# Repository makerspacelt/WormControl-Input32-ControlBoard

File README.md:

---

WormControl Inputs Control board

NOTE: This is only a prototype now, so things might not work and everything might change 

Basic target features:

* Compatibility with esphome and Home Assistant

Dev NOTE: before commit, run `./kibot.sh` to regenerate documentation, bom, gerbers and other assets.

* [schematics.pdf](gen/schematics.pdf)
* [pcb.pdf with dimensions](gen/pcb.pdf)
* [ibom.html](gen/single/ibom.html)

---

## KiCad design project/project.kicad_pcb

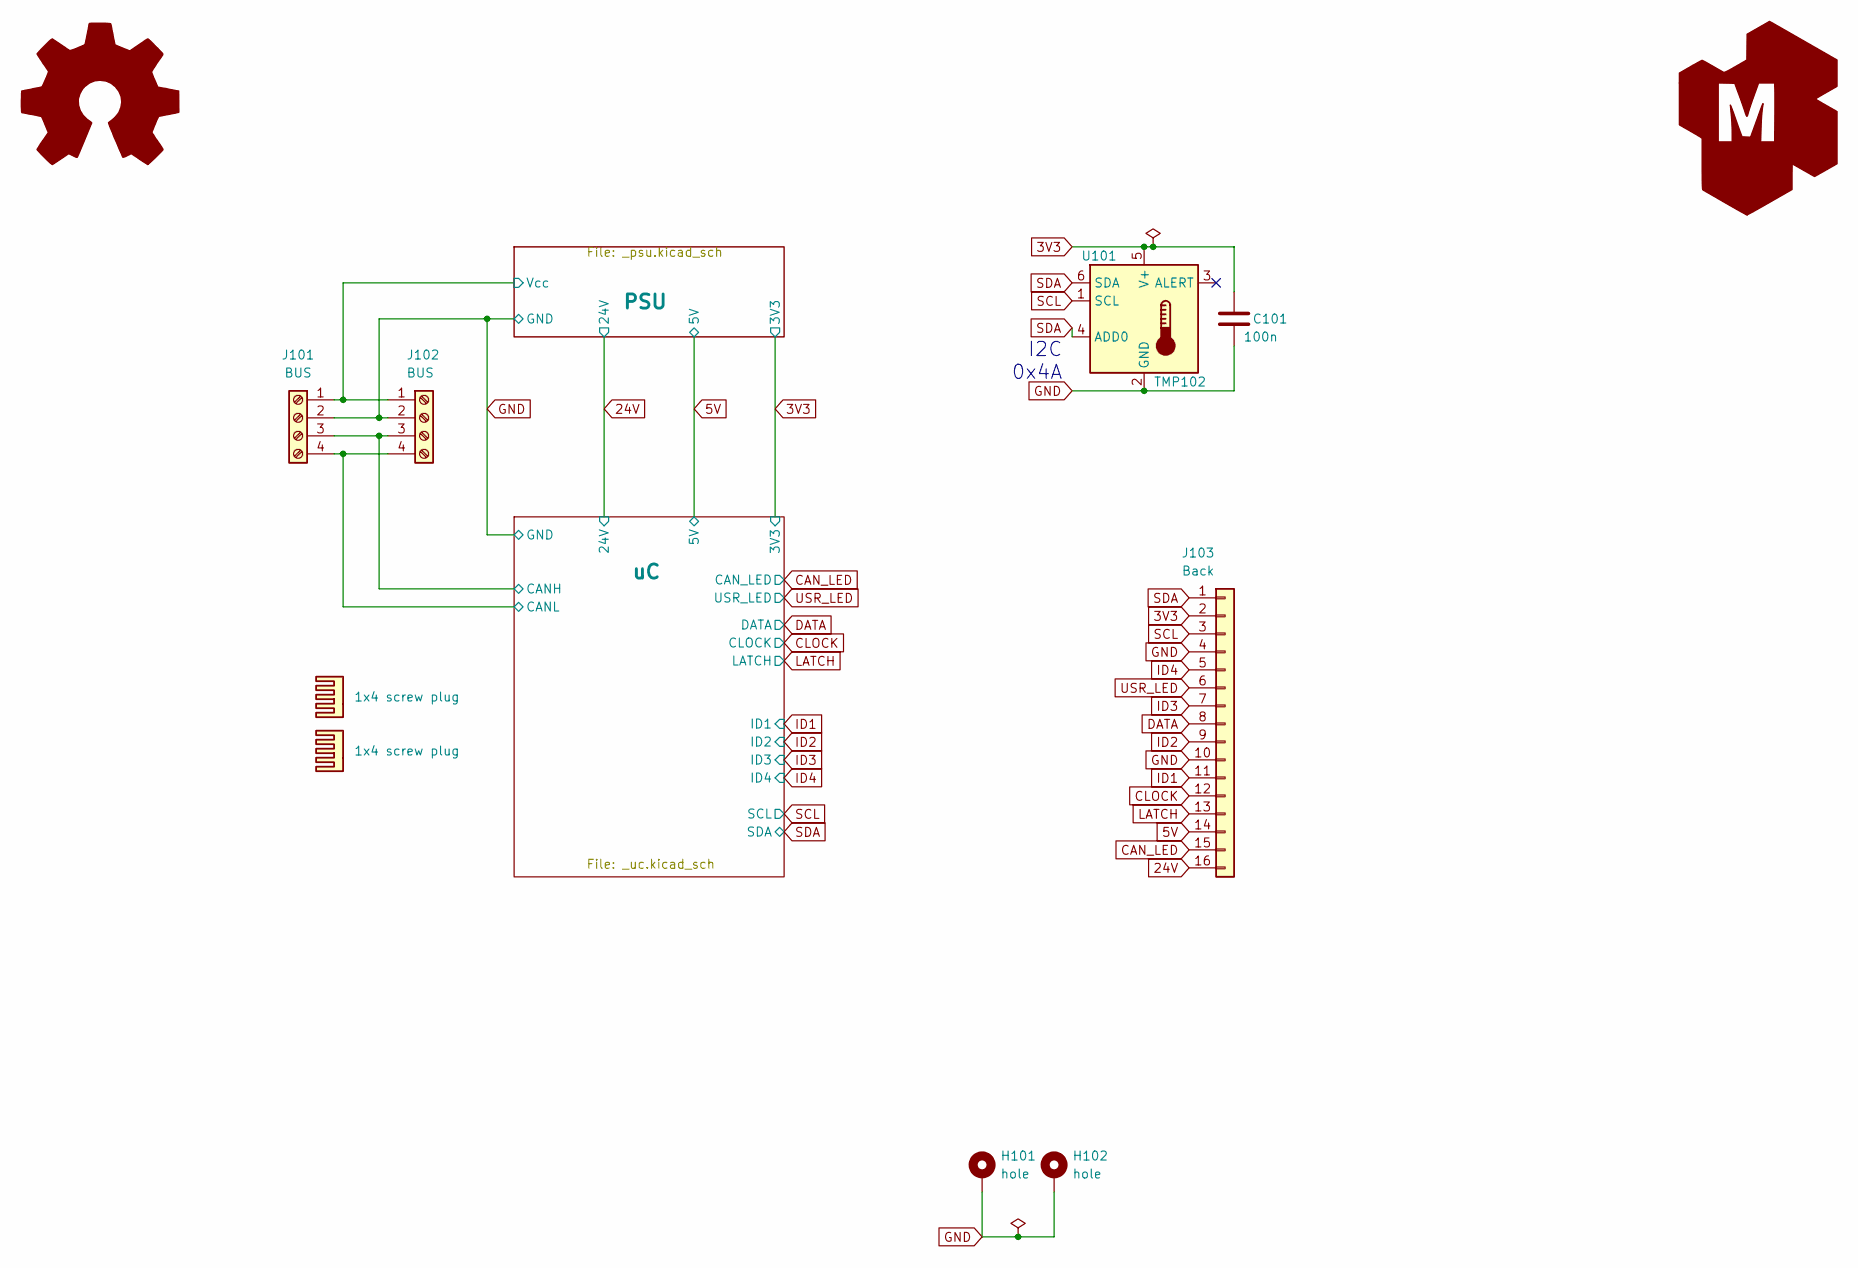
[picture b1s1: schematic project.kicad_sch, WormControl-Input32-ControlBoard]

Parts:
BOM101, BOM102: 1x4 screw plug; jlc-part-type E
C101: 100n; C_0805_2012Metric_Pad1.18x1.45mm_HandSolder; jlc-part-type B
G101: Logo_Open_Hardware_Large; OSHW-Symbol_6.7x6mm_SilkScreen
G102: LOGO_KMS; logo_kms_small_silkscreen
H101, H102: hole; MountingHole_3.2mm_M3_Pad_Via
J101, J102: BUS; PhoenixContact_MCV_1,5_4-G-3.5_1x04_P3.50mm_Vertical; jlc-part-type E
J103: Back; PinSocket_2x08_P2.54mm_Vertical_SMD; lcsc# C3975153
U101: TMP102; SOT-563; jlc-part-type E

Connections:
3V3: C101.1, J103.2, U101.5 (V+); also elsewhere on the board
5V: J103.14; also elsewhere on the board
24V: J103.16; also elsewhere on the board
/PSU/Vcc: J101.1, J102.1; also elsewhere on the board
/uC/CANH: J101.3, J102.3; also elsewhere on the board
/uC/CANL: J101.4, J102.4; also elsewhere on the board
CAN_LED: J103.15; also elsewhere on the board
CLOCK: J103.12; also elsewhere on the board
DATA: J103.8; also elsewhere on the board
GND: C101.2, H101.1, H102.1, J101.2, J102.2, J103.4, J103.10, U101.2 (GND); also elsewhere on the board
ID1: J103.11; also elsewhere on the board
ID2: J103.9; also elsewhere on the board
ID3: J103.7; also elsewhere on the board
ID4: J103.5; also elsewhere on the board
LATCH: J103.13; also elsewhere on the board
SCL: J103.3, U101.1 (SCL); also elsewhere on the board
SDA: J103.1, U101.4 (ADD0), U101.6 (SDA); also elsewhere on the board
USR_LED: J103.6; also elsewhere on the board

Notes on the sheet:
I2C 0x4A

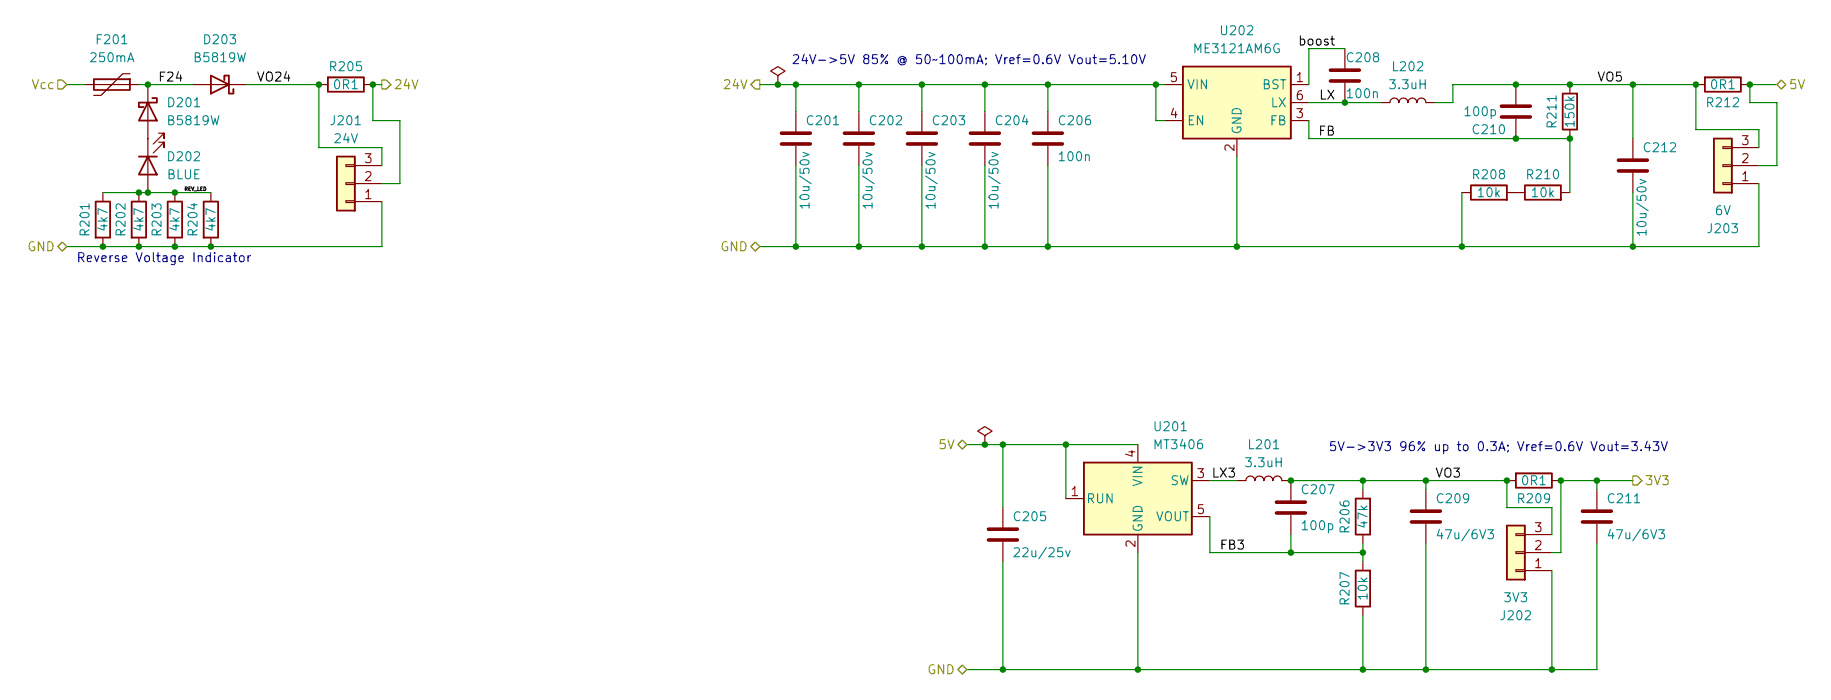
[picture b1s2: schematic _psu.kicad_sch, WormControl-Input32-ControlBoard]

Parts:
C201, C202, C203, C204, C212: 10u/50v; C_0805_2012Metric_Pad1.18x1.45mm_HandSolder; jlc-part-type B
C205: 22u/25v; C_0805_2012Metric_Pad1.18x1.45mm_HandSolder; jlc-part-type B
C206, C208: 100n; C_0805_2012Metric_Pad1.18x1.45mm_HandSolder; jlc-part-type B
C207, C210: 100p; C_0805_2012Metric_Pad1.18x1.45mm_HandSolder; jlc-part-type B
C209, C211: 47u/6V3; C_0805_2012Metric_Pad1.18x1.45mm_HandSolder; jlc-part-type B
D201, D203: B5819W; D_SOD-123; jlc-part-type B
D202: BLUE; LED_0805_2012Metric_Pad1.15x1.40mm_HandSolder; jlc-part-type B
F201: 250mA; Fuse_0805_2012Metric_Pad1.15x1.40mm_HandSolder; lcsc# C22378353
J201: 24V; PinHeader_1x03_P2.54mm_Vertical
J202: 3V3; PinHeader_1x03_P2.54mm_Vertical
J203: 6V; PinHeader_1x03_P2.54mm_Vertical
L201, L202: 3.3uH; L_1008_2520Metric_Pad1.43x2.20mm_HandSolder; jlc-part-type E
R201, R202, R203, R204: 4k7; R_0805_2012Metric_Pad1.20x1.40mm_HandSolder; jlc-part-type B
R205, R209, R212: 0R1; R_0805_2012Metric_Pad1.20x1.40mm_HandSolder; jlc-part-type E
R206: 47k; R_0805_2012Metric_Pad1.20x1.40mm_HandSolder; jlc-part-type B
R207, R208, R210: 10k; R_0805_2012Metric_Pad1.20x1.40mm_HandSolder; jlc-part-type B
R211: 150k; R_0805_2012Metric_Pad1.20x1.40mm_HandSolder; jlc-part-type B
U201: MT3406; TSOT-23-5; jlc-part-type E
U202: ME3121AM6G; SOT-23-6; jlc-part-type E

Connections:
3V3: C211.1, J202.2, R209.1; also elsewhere on the board
5V: C205.1, J203.2, R212.1, U201.1 (RUN), U201.4 (VIN); also elsewhere on the board
24V: C201.1, C202.1, C203.1, C204.1, C206.1, J201.2, R205.1, U202.4 (EN), U202.5 (VIN); also elsewhere on the board
/PSU/F24: D201.1 (K), D203.2 (A), F201.1
/PSU/FB: C210.1, R210.2, R211.1, U202.3 (FB)
/PSU/FB3: C207.2, R206.1, R207.2, U201.5 (VOUT)
/PSU/LX: C208.2, L202.1, U202.6 (LX)
/PSU/LX3: L201.1, U201.3 (SW)
/PSU/REV_LED: D202.2 (A), R201.1, R202.1, R203.1, R204.1
/PSU/VO3: C207.1, C209.1, J202.3, L201.2, R206.2, R209.2
/PSU/VO5: C210.2, C212.1, J203.3, L202.2, R211.2, R212.2
/PSU/VO24: D203.1 (K), J201.3, R205.2
/PSU/Vcc: F201.2; also elsewhere on the board
/PSU/boost: C208.1, U202.1 (BST)
GND: C201.2, C202.2, C203.2, C204.2, C205.2, C206.2, C209.2, C211.2, C212.2, J201.1, J202.1, J203.1, R201.2, R202.2, R203.2, R204.2, R207.1, R208.1, U201.2 (GND), U202.2 (GND); also elsewhere on the board
unnamed: D201.2 (A), D202.1 (K)
unnamed: R208.2, R210.1

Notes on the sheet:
24V->5V 85% @ 50~100mA; Vref=0.6V Vout=5.10V
5V->3V3 96% up to 0.3A; Vref=0.6V Vout=3.43V
Reverse Voltage Indicator

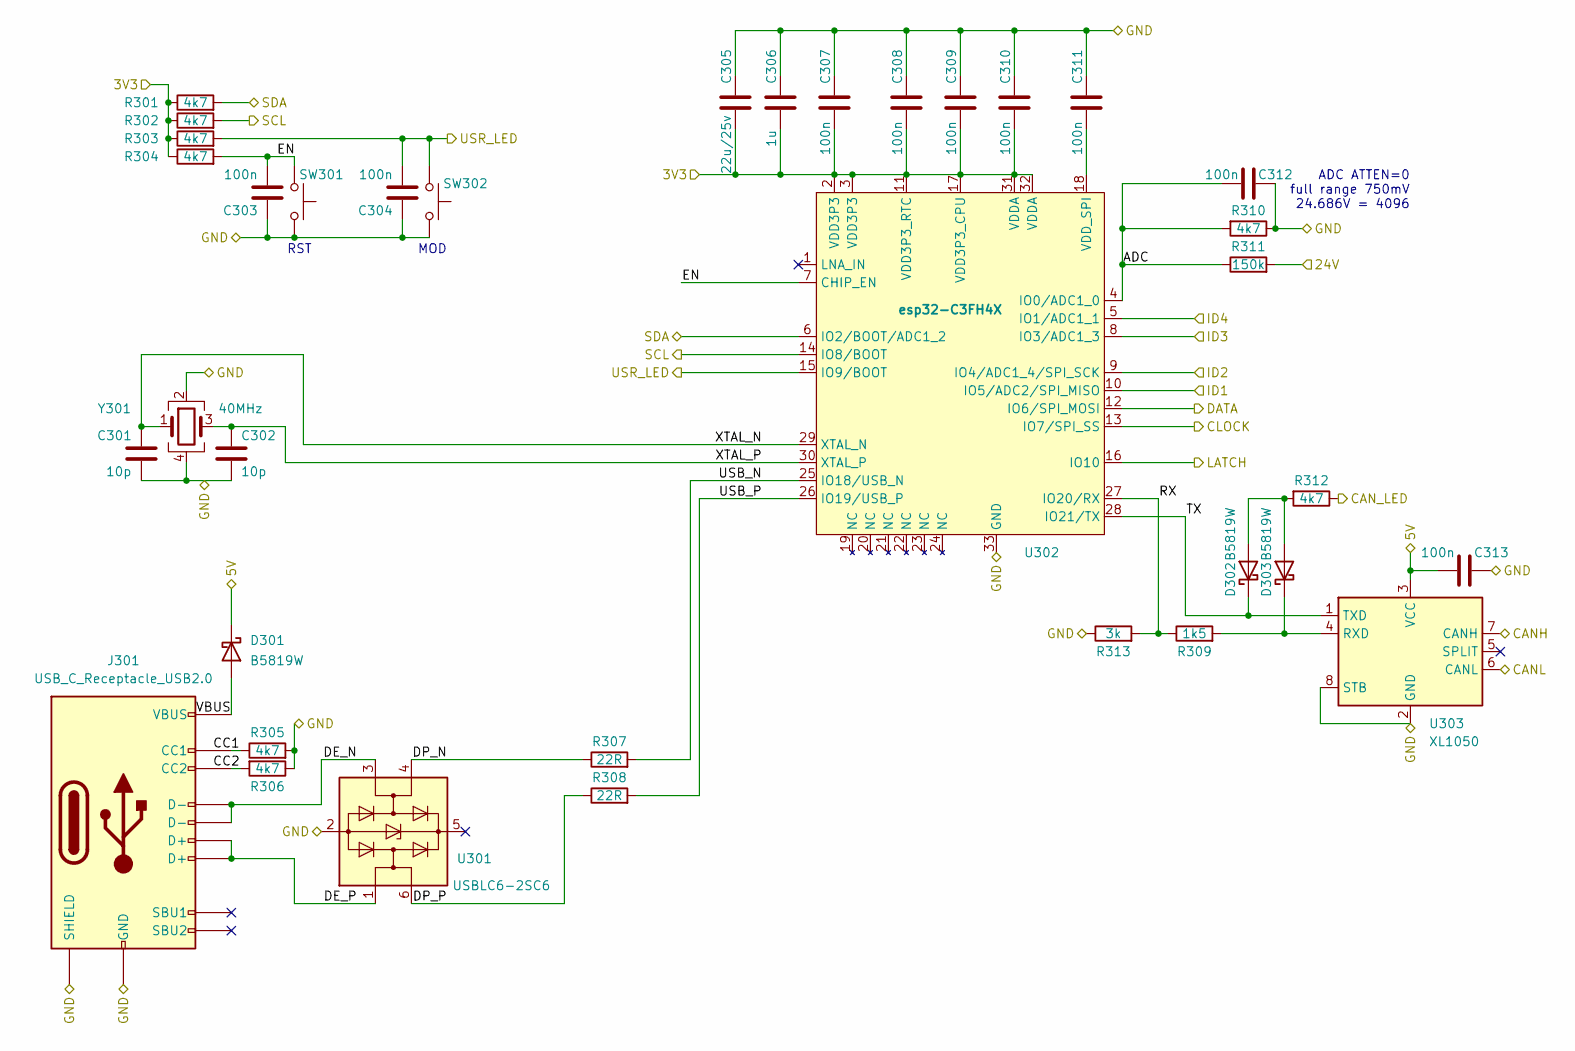
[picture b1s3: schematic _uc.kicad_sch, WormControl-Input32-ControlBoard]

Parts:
C301, C302: 10p; C_0402_1005Metric_Pad0.74x0.62mm_HandSolder; jlc-part-type B
C303, C304, C307, C308, C309, C310, C311, C312, C313: 100n; C_0805_2012Metric_Pad1.18x1.45mm_HandSolder; jlc-part-type B
C305: 22u/25v; C_0805_2012Metric_Pad1.18x1.45mm_HandSolder; jlc-part-type B
C306: 1u; C_0805_2012Metric_Pad1.18x1.45mm_HandSolder; jlc-part-type B
D301, D302, D303: B5819W; D_SOD-123; jlc-part-type B
J301: USB_C_Receptacle_USB2.0; USB_C_Receptacle_G-Switch_GT-USB-7082G; jlc-part-type E
R301, R302, R303, R304, R305, R306, R310, R312: 4k7; R_0805_2012Metric_Pad1.20x1.40mm_HandSolder; jlc-part-type B
R307, R308: 22R; R_0805_2012Metric_Pad1.20x1.40mm_HandSolder; jlc-part-type B
R309: 1k5; R_0805_2012Metric_Pad1.20x1.40mm_HandSolder; jlc-part-type B
R311: 150k; R_0805_2012Metric_Pad1.20x1.40mm_HandSolder; jlc-part-type B
R313: 3k; R_0805_2012Metric_Pad1.20x1.40mm_HandSolder; jlc-part-type B
SW301, SW302: 15mm; SW_SPST_15; jlc-part-type E
U301: USBLC6-2SC6; SOT-23-6; jlc-part-type E
U302: esp32-C3FH4X; QFN-32-1EP_5x5mm_P0.5mm_EP3.65x3.65mm; jlc-part-type E
U303: XL1050; SOIC-8_3.9x4.9mm_P1.27mm; jlc-part-type E
Y301: 40MHz; Crystal_SMD_2016-4Pin_2.0x1.6mm; jlc-part-type E

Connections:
3V3: C305.2, C306.2, C307.1, C308.1, C309.1, C310.1, R301.1, R302.1, R303.1, R304.1, U302.2 (VDD3P3), U302.3 (VDD3P3), U302.11 (VDD3P3_RTC), U302.17 (VDD3P3_CPU), U302.31 (VDDA), U302.32 (VDDA); also elsewhere on the board
5V: C313.1, D301.1 (K), U303.3 (VCC); also elsewhere on the board
24V: R311.2; also elsewhere on the board
/uC/ADC: C312.1, R310.2, R311.1, U302.4 (IO0/ADC1_0)
/uC/CANH: U303.7 (CANH); also elsewhere on the board
/uC/CANL: U303.6 (CANL); also elsewhere on the board
/uC/CC1: J301.A5 (CC1), R305.1
/uC/CC2: J301.B5 (CC2), R306.2
/uC/DE_N: J301.A7 (D-), J301.B7 (D-), U301.3 (I/O2)
/uC/DE_P: J301.A6 (D+), J301.B6 (D+), U301.1 (I/O1)
/uC/DP_N: R307.1, U301.4 (I/O2)
/uC/DP_P: R308.1, U301.6 (I/O1)
/uC/EN: C303.2, R304.2, SW301.1, U302.7 (CHIP_EN)
/uC/RX: R309.1, R313.2, U302.27 (IO20/RX)
/uC/TX: D302.1 (K), U302.28 (IO21/TX), U303.1 (TXD)
/uC/USB_N: R307.2, U302.25 (IO18/USB_N)
/uC/USB_P: R308.2, U302.26 (IO19/USB_P)
/uC/VBUS: D301.2 (A), J301.A4 (VBUS), J301.A9 (VBUS), J301.B4 (VBUS), J301.B9 (VBUS)
/uC/XTAL_N: C301.1, U302.29 (XTAL_N), Y301.1
/uC/XTAL_P: C302.1, U302.30 (XTAL_P), Y301.3
CAN_LED: R312.1; also elsewhere on the board
CLOCK: U302.13 (IO7/SPI_SS); also elsewhere on the board
DATA: U302.12 (IO6/SPI_MOSI); also elsewhere on the board
GND: C301.2, C302.2, C303.1, C304.1, C305.1, C306.1, C307.2, C308.2, C309.2, C310.2, C311.2, C312.2, C313.2, J301.A1 (GND), J301.A12 (GND), J301.B1 (GND), J301.B12 (GND), J301.S1 (SHIELD), R305.2, R306.1, R310.1, R313.1, SW301.2, SW302.2, U301.2 (GND), U302.33 (GND), U303.2 (GND), U303.8 (STB), Y301.2, Y301.4; also elsewhere on the board
ID1: U302.10 (IO5/ADC2/SPI_MISO); also elsewhere on the board
ID2: U302.9 (IO4/ADC1_4/SPI_SCK); also elsewhere on the board
ID3: U302.8 (IO3/ADC1_3); also elsewhere on the board
ID4: U302.5 (IO1/ADC1_1); also elsewhere on the board
LATCH: U302.16 (IO10); also elsewhere on the board
unnamed: C311.1, U302.18 (VDD_SPI)
unnamed: D302.2 (A), D303.2 (A), R312.2
unnamed: D303.1 (K), R309.2, U303.4 (RXD)
SCL: R302.2, U302.14 (IO8/BOOT); also elsewhere on the board
SDA: R301.2, U302.6 (IO2/BOOT/ADC1_2); also elsewhere on the board
USR_LED: C304.2, R303.2, SW302.1, U302.15 (IO9/BOOT); also elsewhere on the board

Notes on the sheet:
RST
ADC ATTEN=0 full range 750mV 24.686V = 4096
MOD

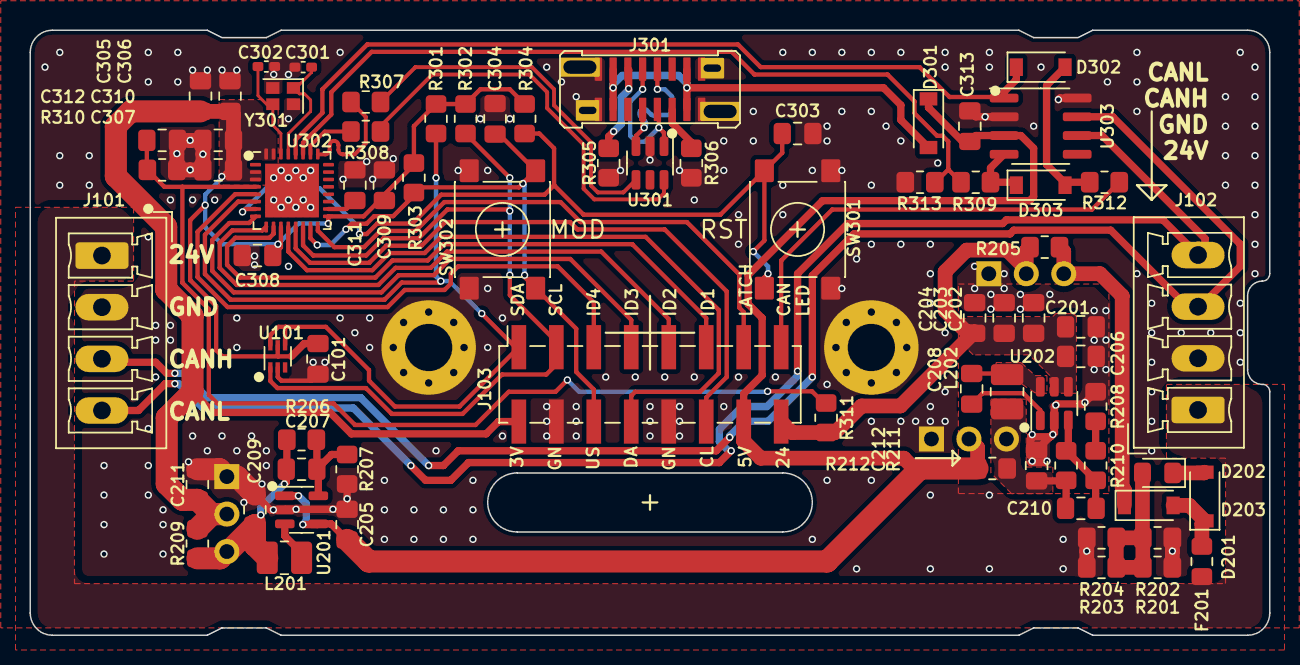
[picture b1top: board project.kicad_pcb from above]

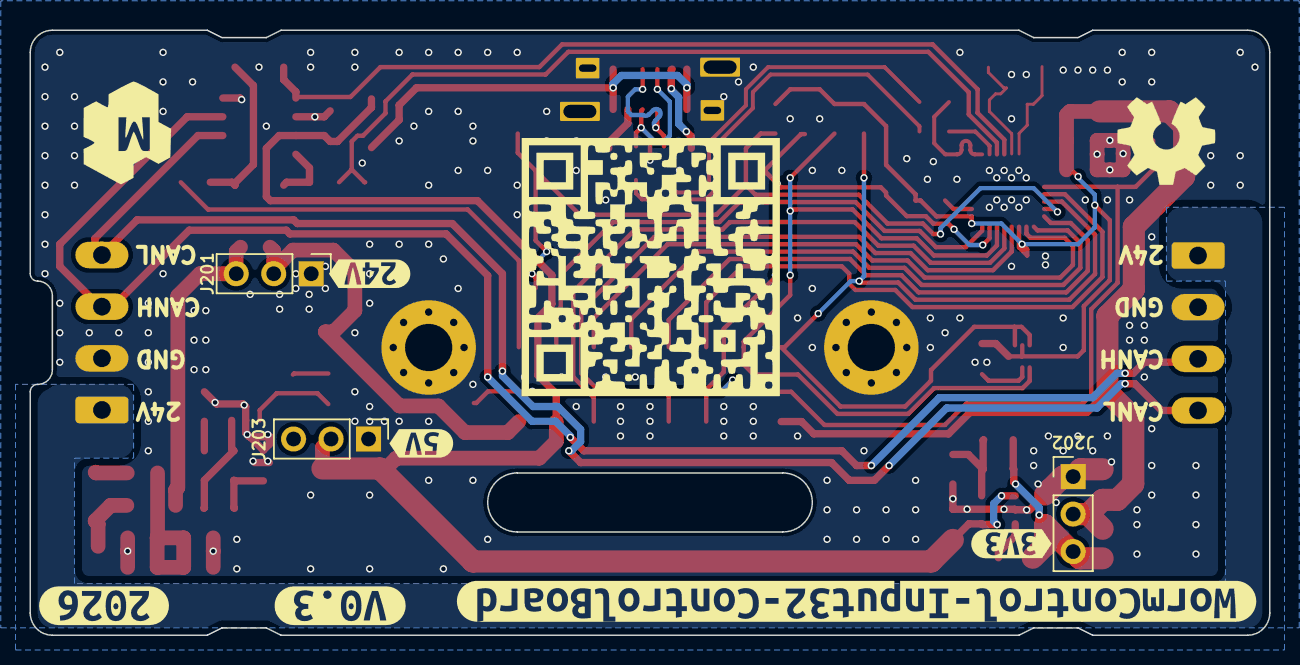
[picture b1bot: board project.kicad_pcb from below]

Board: 4 copper layers, 84.0 x 41.0 mm, 86 parts (11 on the bottom side), 48 nets.

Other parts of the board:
kibuzzard-6A7A000F: G***; kibuzzard-6A7A000F
kibuzzard-68F6C776: G***; kibuzzard-68F6C776
kibuzzard-69BC7F29: G***; kibuzzard-69BC7F29
kibuzzard-698AF99F: G***; kibuzzard-698AF99F
kibuzzard-698C575A: G***; kibuzzard-698C575A
kibuzzard-698C579F: G***; kibuzzard-698C579F

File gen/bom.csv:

"Row","Description","Part","References","Value","Footprint","Quantity Per PCB","Status","Datasheet","lcsc#","jlc-part-type"
"1","Heatsink","Heatsink","BOM101,BOM102","1x4 screw plug","","2"," ","https://www.lcsc.com/datasheet/lcsc_datasheet_2309070925_DEG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","C7603442","E"
"2","Unpolarized capacitor","C","C301,C302","10p","C_0402_1005Metric_Pad0.74x0.62mm_HandSolder","2"," ","~","C32949","B"
"3","Unpolarized capacitor","C","C207,C210","100p","C_0805_2012Metric_Pad1.18x1.45mm_HandSolder","2"," ","https://www.lcsc.com/datasheet/lcsc_datasheet_2304140030_Sam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","C1790","B"
"4","Unpolarized capacitor","C","C101,C206,C208,C303,C304,C307,C308,C309,C310,C311,C312,C313","100n","C_0805_2012Metric_Pad1.18x1.45mm_HandSolder","12"," ","https://www.lcsc.com/datasheet/lcsc_datasheet_2304140030_Sam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","C28233","B"
"5","Unpolarized capacitor","C","C306","1u","C_0805_2012Metric_Pad1.18x1.45mm_HandSolder","1"," ","https://www.lcsc.com/datasheet/lcsc_datasheet_2304140030_Sam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","C28323","B"
"6","Unpolarized capacitor","C","C201,C202,C203,C204,C212","10u/50v","C_0805_2012Metric_Pad1.18x1.45mm_HandSolder","5"," ","https://www.lcsc.com/datasheet/lcsc_datasheet_2411041759_Mur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","C440198","B"
"7","Unpolarized capacitor","C","C205,C305","22u/25v","C_0805_2012Metric_Pad1.18x1.45mm_HandSolder","2"," ","https://www.lcsc.com/datasheet/lcsc_datasheet_2304140030_Sam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","C45783","B"
"8","Unpolarized capacitor","C","C209,C211","47u/6V3","C_0805_2012Metric_Pad1.18x1.45mm_HandSolder","2"," ","https://www.lcsc.com/datasheet/C16780.pdf","C16780","B"
"9","Schottky diode","D_Schottky","D201,D203,D301,D302,D303","B5819W","D_SOD-123","5"," ","https://www.lcsc.com/datasheet/lcsc_datasheet_2304140030_Jia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","C8598","B"
"10","Light emitting diode","LED","D202","BLUE","LED_0805_2012Metric_Pad1.15x1.40mm_HandSolder","1"," ","https://www.lcsc.com/datasheet/C2297.pdf","C2297","B"
"11","Resettable fuse, polymeric positive temperature coefficient","Polyfuse","F201","250mA","Fuse_0805_2012Metric_Pad1.15x1.40mm_HandSolder","1"," ","https://wmsc.lcsc.com/wmsc/upload/file/pdf/v2/lcsc/240408162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","C22378353","E"
"12","Generic connector, single row, 01x03, script generated (kicad-library-utils/schlib/autogen/connector/)","Conn_01x03","J201,J202,J203","24V","PinHeader_1x03_P2.54mm_Vertical","3"," ","~","","-"
"13","Generic screw terminal, single row, 01x04, script generated (kicad-library-utils/schlib/autogen/connector/)","Screw_Terminal_01x04","J101,J102","BUS","PhoenixContact_MCV_1,5_4-G-3.5_1x04_P3.50mm_Vertical","2"," ","https://www.lcsc.com/datasheet/lcsc_datasheet_2304140030_Nin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","C880556","E"
"14","Generic connector, single row, 01x16, script generated (kicad-library-utils/schlib/autogen/connector/)","Conn_01x16","J103","Back","PinSocket_2x08_P2.54mm_Vertical_SMD","1"," ","https://wmsc.lcsc.com/wmsc/upload/file/pdf/v2/lcsc/230609101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","C3975153","E"
"15","USB 2.0-only Type-C Receptacle connector","USB_C_Receptacle_USB2.0","J301","USB_C_Receptacle_USB2.0","USB_C_Receptacle_G-Switch_GT-USB-7082G","1"," ","https://www.lcsc.com/datasheet/lcsc_datasheet_2405271642_G-S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","C22383836","E"
"16","Inductor","L","L201,L202","3.3uH","L_1008_2520Metric_Pad1.43x2.20mm_HandSolder","2"," ","https://www.lcsc.com/datasheet/C5832373.pdf","C5832373","E"
"17","Resistor","R","R205,R209,R212","0R1","R_0805_2012Metric_Pad1.20x1.40mm_HandSolder","3"," ","https://www.lcsc.com/datasheet/lcsc_datasheet_2304140030_UNI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","C127687","E"
"18","Resistor","R","R307,R308","22R","R_0805_2012Metric_Pad1.20x1.40mm_HandSolder","2"," ","~","C17561","B"
"19","Resistor","R","R309","1k5","R_0805_2012Metric_Pad1.20x1.40mm_HandSolder","1"," ","~","C4310","B"
"20","Resistor","R","R313","3k","R_0805_2012Metric_Pad1.20x1.40mm_HandSolder","1"," ","~","C17661","B"
"21","Resistor","R","R201,R202,R203,R204,R301,R302,R303,R304,R305,R306,R310,R312","4k7","R_0805_2012Metric_Pad1.20x1.40mm_HandSolder","12"," ","~","C17673","B"
"22","Resistor","R","R207,R208,R210","10k","R_0805_2012Metric_Pad1.20x1.40mm_HandSolder","3"," ","~","C17414","B"
"23","Resistor","R","R206","47k","R_0805_2012Metric_Pad1.20x1.40mm_HandSolder","1"," ","~","C17713","B"
"24","Resistor","R","R211,R311","150k","R_0805_2012Metric_Pad1.20x1.40mm_HandSolder","2"," ","~","C17470","B"
"25","Push button switch, generic, two pins","SW_Push","SW301,SW302","15mm","SW_SPST_15","2"," ","https://www.lcsc.com/datasheet/lcsc_datasheet_2110120830_XKB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","C2885154","E"
"26","1.2 A Simple Buck Regulator, 3-26V input, 1.5Mhz","AOZ1280CI","U202","ME3121AM6G","SOT-23-6","1"," ","https://m.huazhoucn.com/upFiles/common/2022/12/ME3121_Series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","C2932938","E"
"27","600mA Synchronous Step-Down Regulator, 1.5MHz, Adjustable Output Voltage, Burst Mode, ThinSOT-23","LTC3406ES5","U201","MT3406","TSOT-23-5","1"," ","https://www.lcsc.com/datasheet/lcsc_datasheet_2406131737_XI-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","C22462728","E"
"28","Digital Temperature Sensor, +/- 3 °C, low-Power, SMBus, 12 bit, Two-Wire Serial Interface, SOT-563","TMP102xxDRL","U101","TMP102","SOT-563","1"," ","https://www.ti.com/lit/ds/symlink/tmp102.pdf","C99269","E"
"29","Very low capacitance ESD protection diode, 2 data-line, SOT-23-6","USBLC6-2SC6","U301","USBLC6-2SC6","SOT-23-6","1"," ","https://www.lcsc.com/datasheet/lcsc_datasheet_2311091738_UMW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","C2687116","E"
"30","High-Speed CAN Transceiver, standby mode, split pin, SOIC-8","TJA1042T","U303","XL1050","SOIC-8_3.9x4.9mm_P1.27mm","1"," ","https://www.lcsc.com/datasheet/lcsc_datasheet_2309141025_XIN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","C609746","E"
"31","esp32-C3FH4X 4MB flash QFN32-1EP 5x5mm EP3.7x3.7mm","esp32-C3FH4X","U302","esp32-C3FH4X","QFN-32-1EP_5x5mm_P0.5mm_EP3.65x3.65mm","1"," ","https://www.espressif.com/sites/default/files/documentation/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","C2858491","E"
"32","Four pin crystal, GND on pins 2 and 4","Crystal_GND24","Y301","40MHz","Crystal_SMD_2016-4Pin_2.0x1.6mm","1"," ","https://www.lcsc.com/datasheet/C20885029.pdf","C20885029","E"

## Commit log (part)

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2026-02-12 initial prototype
2026-02-12 updating kibot and generatables
2026-03-19 fixes after preliminary testing
    * Switching to TMP102 as TMP101 is no longer available
    * Removing 5V LDO with OVP as it caused more problems
    * bumping up version
2026-04-20 fixing tmp102 pinout
